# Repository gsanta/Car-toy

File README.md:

# Car-toy

How to start arduino ide:

cd Documents
./arduino-ide_2.3.6_Linux_64bit.AppImage --no-sandbox

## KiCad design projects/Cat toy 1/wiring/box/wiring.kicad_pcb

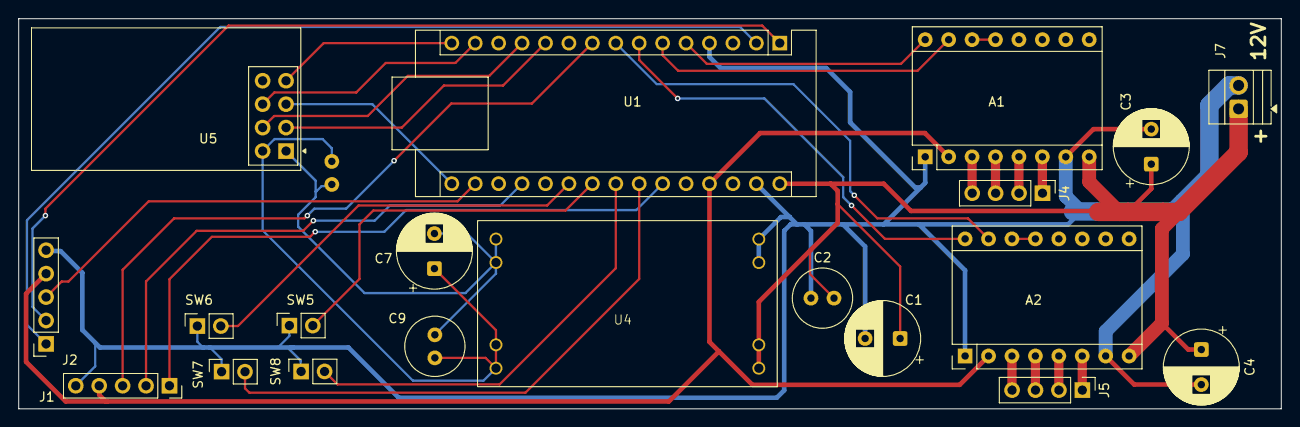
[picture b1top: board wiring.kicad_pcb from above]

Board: 2 copper layers, 136.9 x 42.3 mm, 21 parts (1 on the bottom side), 31 nets.

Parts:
A1, A2: Pololu_Breakout_A4988; Pololu_Breakout-16_15.2x20.3mm
C1, C7: 10uF; CP_Radial_D8.0mm_P3.80mm
C2, C5, C9: 0.1uF; C_Radial_D6.3mm_H7.0mm_P2.50mm
C3, C4: 100mF; CP_Radial_D8.0mm_P3.80mm
J1, J2: Conn_01x05_Pin; PinSocket_1x05_P2.54mm_Vertical
J4, J5: Conn_01x04_Pin; PinHeader_1x04_P2.54mm_Vertical
J7: Conn_01x02_Pin; TerminalBlock_Xinya_XY308-2.54-2P_1x02_P2.54mm_Horizontal
SW5, SW6, SW7, SW8: Conn_01x02_Pin; PinSocket_1x02_P2.54mm_Vertical
U1: Arduino_Nano_v3.x; Arduino_Nano
U4: Mini560-pro-3.3V
U5: NRF24L01_Breakout; nRF24L01_Breakout

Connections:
+3.3V: J2.3, U1.17 (3V3)
+5V: A1.2 (VDD), A1.13 (~RESET), A1.14 (~SLEEP), A2.2 (VDD), A2.13 (~RESET), A2.14 (~SLEEP), J1.4, J2.4, U1.27 (+5V)
+12V: A1.8 (VMOT), A2.8 (VMOT), C1.1, C2.2, C3.1, C4.1, J7.1, U1.30 (VIN), U4.1 (IN+)
/A0_Pin: J1.2, U1.19 (A0)
/A6_Pin: J1.1, U1.25 (A6)
/D0_RX: J2.1, U1.2 (D0/RX)
/D1_TX: J2.2, U1.1 (D1/TX)
/D6_Pin: J1.3, U1.9 (D6)
/LIM_E: SW8.2, U1.23 (A4)
/LIM_N: SW5.2, U1.22 (A3)
/LIM_S: SW6.2, U1.21 (A2)
/LIM_W: SW7.2, U1.24 (A5)
/MOT1_DIR: A1.16 (DIR), U1.5 (D2)
/MOT1_STEP: A1.15 (STEP), U1.6 (D3)
/MOT2_DIR: A2.16 (DIR), U1.7 (D4)
/MOT2_STEP: A2.15 (STEP), U1.8 (D5)
/R_CE: U1.11 (D8), U5.3 (CE)
/R_CSN: U1.12 (D9), U5.4 (~CSN)
/R_MISO: U1.15 (D12), U5.7 (MISO)
/R_MOSI: U1.14 (D11), U5.6 (MOSI)
/R_SCK: U1.16 (D13), U5.5 (SCK)
/Radio/3.3V: C5.1, C7.1, C9.1, U4.3 (OUT+), U5.2 (VCC)
GND: A1.1 (GND), A1.7 (GND), A2.1 (GND), A2.7 (GND), C1.2, C2.1, C3.2, C4.2, C5.2, C7.2, C9.2, J1.5, J2.5, J7.2, SW5.1, SW6.1, SW7.1, SW8.1, U1.4 (GND), U1.29 (GND), U4.2 (IN-), U4.4 (OUT-), U5.1 (GND)
unnamed: A1.4 (1A), J4.3
unnamed: A1.3 (1B), J4.4
unnamed: A1.5 (2A), J4.2
unnamed: A1.6 (2B), J4.1
unnamed: A2.4 (1A), J5.3
unnamed: A2.3 (1B), J5.4
unnamed: A2.5 (2A), J5.2
unnamed: A2.6 (2B), J5.1

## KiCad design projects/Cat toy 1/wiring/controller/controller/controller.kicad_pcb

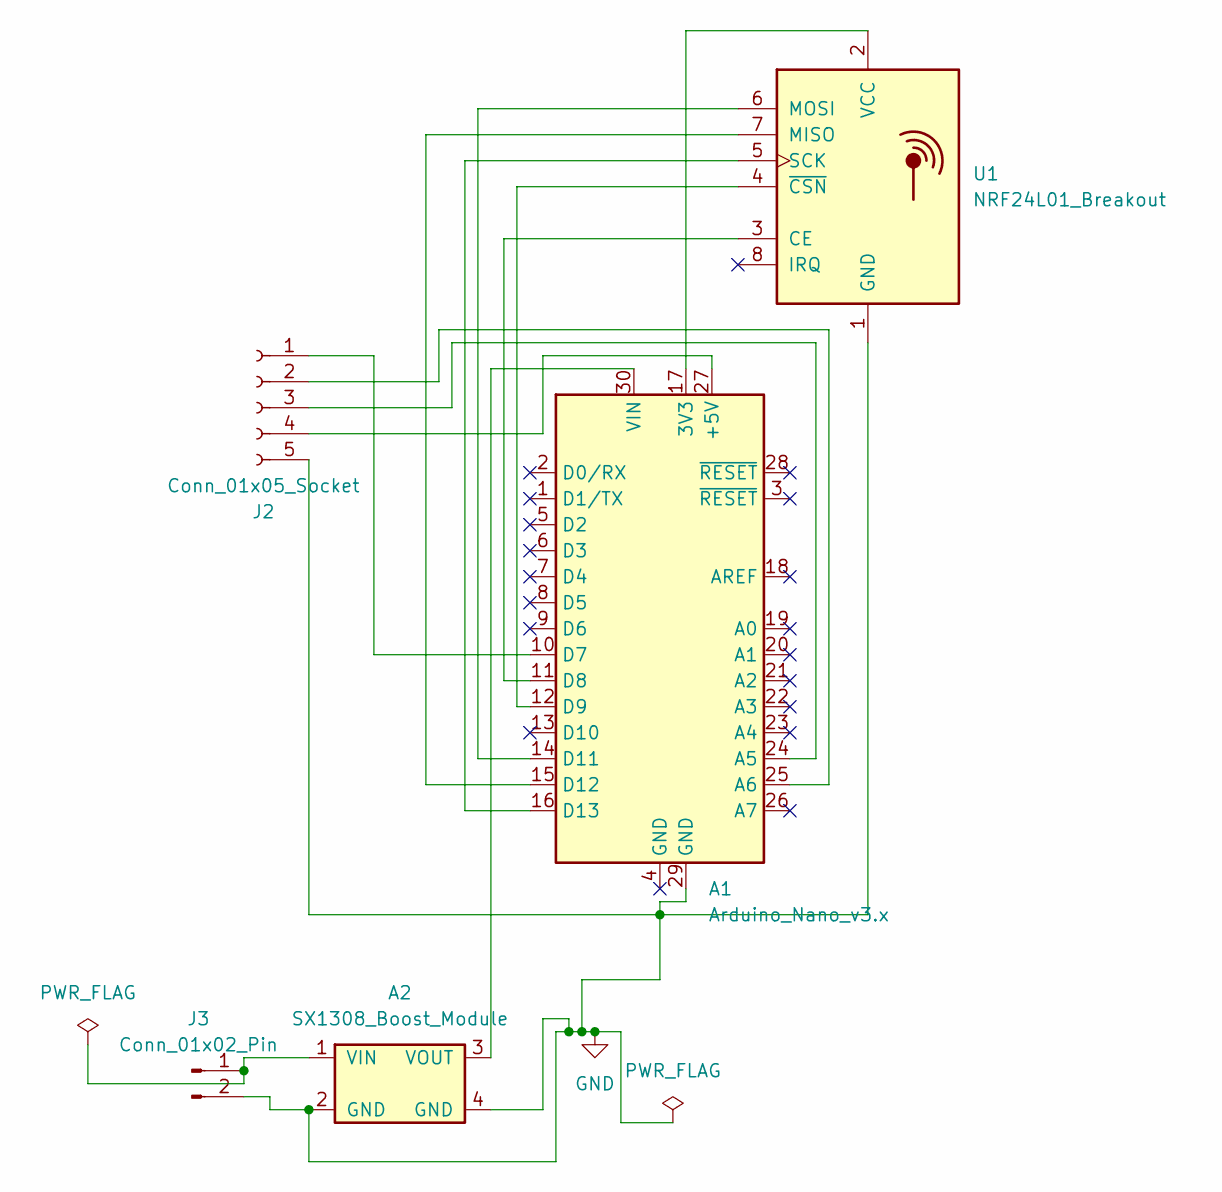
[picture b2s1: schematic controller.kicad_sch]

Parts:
A1: Arduino_Nano_v3.x; Arduino_Nano
A2: SX1308_Boost_Module
J2: Conn_01x05_Socket; PinSocket_1x05_P2.54mm_Horizontal
J3: Conn_01x02_Pin; PinHeader_1x02_P2.54mm_Vertical
U1: NRF24L01_Breakout; nRF24L01_Breakout

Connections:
GND: A1.29 (GND), A2.2 (GND), A2.4 (GND), J2.5, J3.2, U1.1 (GND)
unnamed: A1.17 (3V3), U1.2 (VCC)
unnamed: A1.27 (+5V), J2.4
unnamed: A1.24 (A5), J2.3
unnamed: A1.25 (A6), J2.2
unnamed: A1.10 (D7), J2.1
unnamed: A1.11 (D8), U1.3 (CE)
unnamed: A1.12 (D9), U1.4 (~CSN)
unnamed: A1.14 (D11), U1.6 (MOSI)
unnamed: A1.15 (D12), U1.7 (MISO)
unnamed: A1.16 (D13), U1.5 (SCK)
unnamed: A1.30 (VIN), A2.3 (VOUT)
unnamed: A2.1 (VIN), J3.1

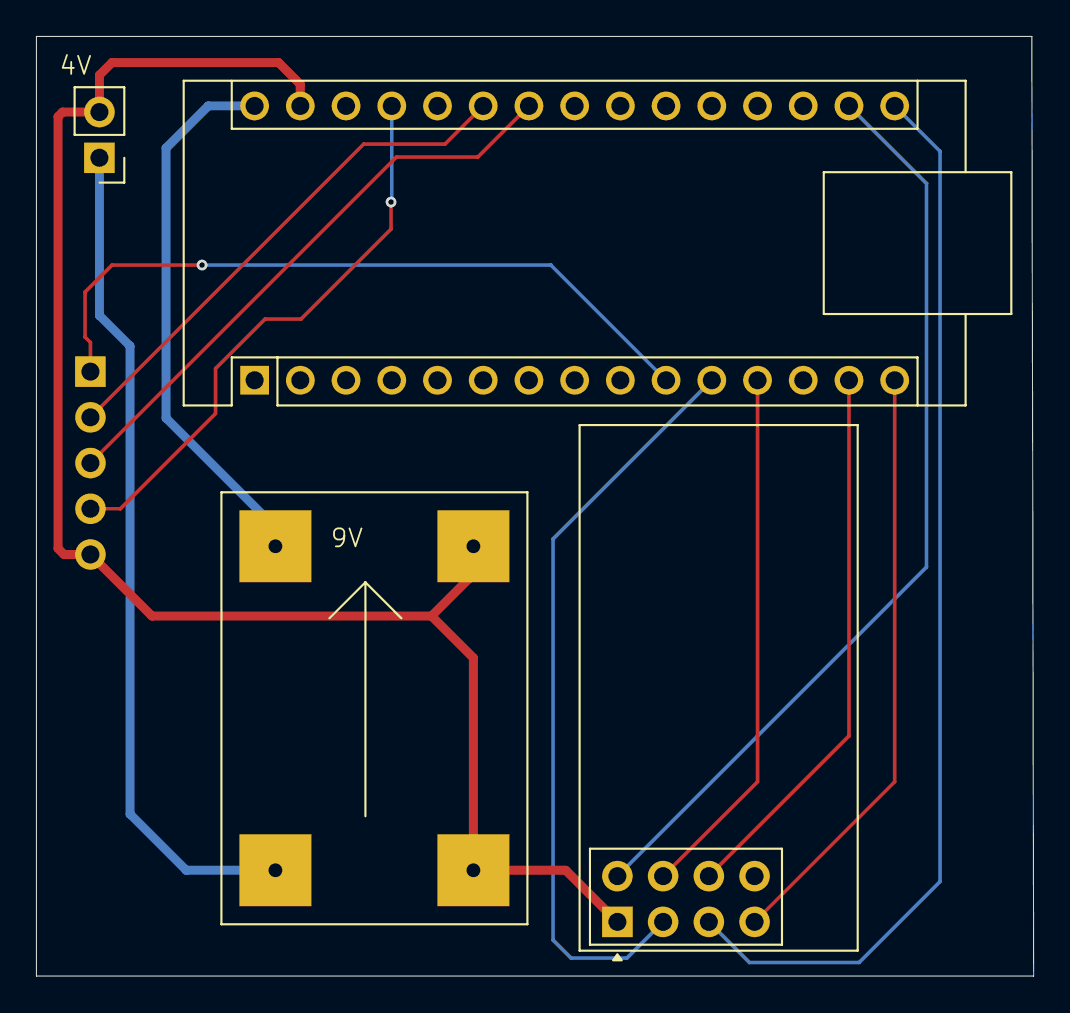
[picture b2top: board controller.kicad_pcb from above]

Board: 2 copper layers, 55.4 x 52.2 mm, 5 parts (0 on the bottom side), 13 nets.

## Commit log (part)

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2025-09-15 Turning
2025-10-18 interface for dc motor
2025-10-26 stepper motor
2025-12-02 Add temperature projects
2025-12-03 Motion detector
2025-12-06 Obstacle detector
2025-12-16 stepper motor lib, motor project added
2025-12-21 House project
2025-12-25 IR receiver, stepper setup
2026-01-01 BeltDriver
2026-01-02 Finish
2026-01-12 Add joystick
2026-01-14 Movin with joystick
2026-01-28 Progress
2026-01-30 Finish radio transmitter example
2026-01-31 Joystick redesigned
2026-02-01 Joystick and radio transmitter examples
2026-02-14 Refactor belt driver
2026-02-15 cleanup
2026-02-16 working example
2026-02-17 Fixes
2026-03-20 Blender
2026-03-20 KiCad
2026-05-26 Remove unused files
